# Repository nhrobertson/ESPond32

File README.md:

# ESPond32

A custom, self-hosted pond control system. An ESP32-S3 unit drives two pumps, a
water-fill valve, and a light, monitors pond water level with a float sensor, and is
controlled from a small web dashboard running on a Raspberry Pi over the local network.
It is the spiritual successor to the earlier, much simpler PondPi.

The device has no on-board web UI by design. All remote control happens over MQTT
between the firmware and the home server; the physical unit is fully functional on its
own (schedules, switches, leak lockout) even with the network down.

## System overview

```
  3-position switches          Raspberry Pi 3
  float sensor          WiFi   +-----------------------+
        |                LAN   | Mosquitto (MQTT broker)|
   +----v-----------+   <----> | espond-home-server     |  <-- browser
   | ESP32-S3 unit  |   MQTT   | (FastAPI dashboard)    |      (LAN / HTTPS)
   | (firmware)     |          +-----------------------+
   +----+-----------+
        | 3V3 GPIO
   +----v-----------+
   | SSR / relay    | ---> mains ---> pumps, valve, light
   +----------------+
```

- The firmware resolves output state from a strict precedence chain: leak lockout >
  physical switch > network override > schedule.
- The home server is the durable source of truth for configuration and schedules; the
  device only stores the last-applied config version.
- The MQTT wire contract between the two is documented in
  `software/espond-home-server/SPEC.md`.

## Repository layout

| Path | What it is |
|---|---|
| `software/espond32/` | Device firmware (ESP-IDF, C). See its README. |
| `software/espond-home-server/` | Raspberry Pi web dashboard + MQTT bridge (Python/FastAPI). See its README. |
| `hardware/` | KiCad projects (on-board and off-board SSR variants), BOMs, datasheets. See its README. |
| `ai_design_doc.pdf` | Original "Pond Control Unit — Design & Build Plan." Guidelines only; see disclosure below. |
| `LICENSE.md` | GNU GPL v3. |

## How this project was built (disclosure)

This repository mixes hand-written and AI-generated work, and it matters which is which:

- The **firmware** (`software/espond32/`) and the **hardware** (`hardware/`) were designed
  and written by hand by the project owner, with only minimal AI assistance.
- The **home server** (`software/espond-home-server/`) was generated almost entirely by an
  AI coding agent (Claude Code) working from a hand-authored spec. It has been deployed and
  works well, but should be reviewed like any AI-written code — particularly the auth and
  MQTT-handling paths — before being exposed beyond a trusted home LAN.
- `ai_design_doc.pdf` was an early planning document. It is **not** an accurate description
  of how the device actually works today; it is kept for historical context only. Where it
  conflicts with the firmware or `SPEC.md`, the firmware and `SPEC.md` win.

## Status

The off-board SSR hardware variant is finalized and in manufacturing. The firmware runs on
ESP32-S3 (developed/validated on a DevKitC). The home server is deployed on a Raspberry Pi 3.

## Safety

This system switches mains-voltage loads. Mains wiring, fusing, and enclosure work are the
integrator's responsibility. The float-fill and leak-lockout logic are failsafes, not
substitutes for correct plumbing, a hardware overflow path, and proper electrical practice.
Do not connect this to mains and water without understanding the whole chain.

## License

GNU General Public License v3. See `LICENSE.md`.

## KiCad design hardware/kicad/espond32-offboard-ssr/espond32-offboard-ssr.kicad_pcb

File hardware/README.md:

# ESPond32 Hardware

KiCad projects and supporting documents for the ESPond32 control board. The board carries
the ESP32-S3-WROOM-1 module, per-channel 3-position switches, the float-sensor input, a
WS2812 status LED chain, and the output-driver stage for four channels (pump1, pump2,
valve1, light1).

Designed by hand with only minimal AI assistance.

## Two board variants

There are two KiCad projects under `kicad/`, differing only in how the mains load is
switched:

| Project | Output stage | Mains on board? | Status |
|---|---|---|---|
| `kicad/espond32-offboard-ssr/` | 3.3V/5V logic-level control signal to an **external** SSR / relay module, driven through a MOSFET buffer | No - board is entirely SELV/low-voltage | **Finalized, in manufacturing** |
| `kicad/espond32-onboard-ssr/` | On-board optotriac + power triac SSR stage, mains terminals on the PCB | Yes | Design variant / reference |

The off-board variant is the primary build. It keeps all mains wiring off the PCB (each
channel just sinks an external module's control line to ground), which greatly simplifies
safety, layout, and enclosure work. The on-board variant is kept for anyone who wants a
single-board solution and is comfortable with mains-on-PCB design; it carries fuse, MOV,
isolated AC-DC, and per-channel triac + snubber parts.

Both variants match the firmware exactly: four output channels (not three), the WS2812 LED
chain on GPIO10, and the switch/float pin map from the firmware's `config.h`.

## Folder layout

```
hardware/
  kicad/
    espond32-offboard-ssr/   # primary board - schematic, PCB, exported BOM/CPL, JLCPCB output
    espond32-onboard-ssr/    # on-board-SSR variant
  bom/                       # STALE - see below
  datasheets/                # ESP32-S3-WROOM-1 datasheet
```

## Bill of materials

**The `bom/` folder at the top level is stale. Do not order from it.** The authoritative BOM
for each board is the one exported from its KiCad project (the `.csv` files inside each
`kicad/espond32-*/` directory, and the `jlcpcb/` outputs for the off-board variant). Treat
the KiCad project as the single source of truth for parts, footprints, and designators; the
top-level `bom/` CSVs predate the current schematics and are kept only for reference.

Key part choices worth knowing before a re-spin (from the current design):

- **Module:** ESP32-S3-WROOM-1-**N8** specifically (quad flash, no PSRAM). The N8R8/N16R8
  PSRAM variants use GPIO33-37, which collide with the firmware's debug test points.
- **Off-board output stage:** logic-level N-channel MOSFET (e.g. 2N7000) per channel buffers
  the GPIO up to a full logic swing before it reaches the external SSR/relay module, so the
  design works with the widest range of off-the-shelf 3-32 VDC modules. The external SSR
  modules themselves are not part of the board BOM.
- **Switches:** one 3-position center-off (ON/AUTO/OFF) toggle per channel; common to 3V3,
  the two throws to the SW-A/SW-B GPIOs. No external pulls (firmware configures pull-downs).
- **Float input:** TVS + series resistor + RC filter, sized for a long outdoor sensor run.
- **Indicators:** a single 6-pixel WS2812B chain (pump1, pump2, valve1, light1, float, sys),
  not discrete LEDs.

## KiCad libraries

The ESP32-S3-WROOM-1 symbol/footprint come from Espressif's official KiCad library
(install via KiCad's Plugin & Content Manager). Standard passives use the built-in KiCad
libraries. A few parts (3-position switch, some connectors) use custom footprints built from
their datasheets - see the project's footprint library.

## Manufacturing (off-board variant)

The `kicad/espond32-offboard-ssr/jlcpcb/` directory holds the Gerber/BOM/CPL output prepared
for JLCPCB assembly. Regenerate it from KiCad if you change the board; do not hand-edit the
exported files.

## Safety

The off-board board is low-voltage only and safe to handle and power from USB-C or a 5V
supply. Mains switching happens entirely in the external SSR modules and their wiring
harness - fusing, strain relief, and enclosure/creepage are the integrator's responsibility.

The on-board-SSR variant puts mains on the PCB and is only for people competent with
mains-voltage design: verify fuse rating, MOV placement, isolation/creepage clearances, and
snubber sizing against your actual loads before powering it.

## Provenance and disclosure

This hardware was designed by hand with minimal AI assistance. Note that `ai_design_doc.pdf`
(repo root) is an early planning document - it specifies three output channels and discrete
indicator LEDs, whereas the shipping design has four channels and a WS2812 chain to match the
firmware. Where the design doc and the KiCad projects disagree, the KiCad projects are
correct.

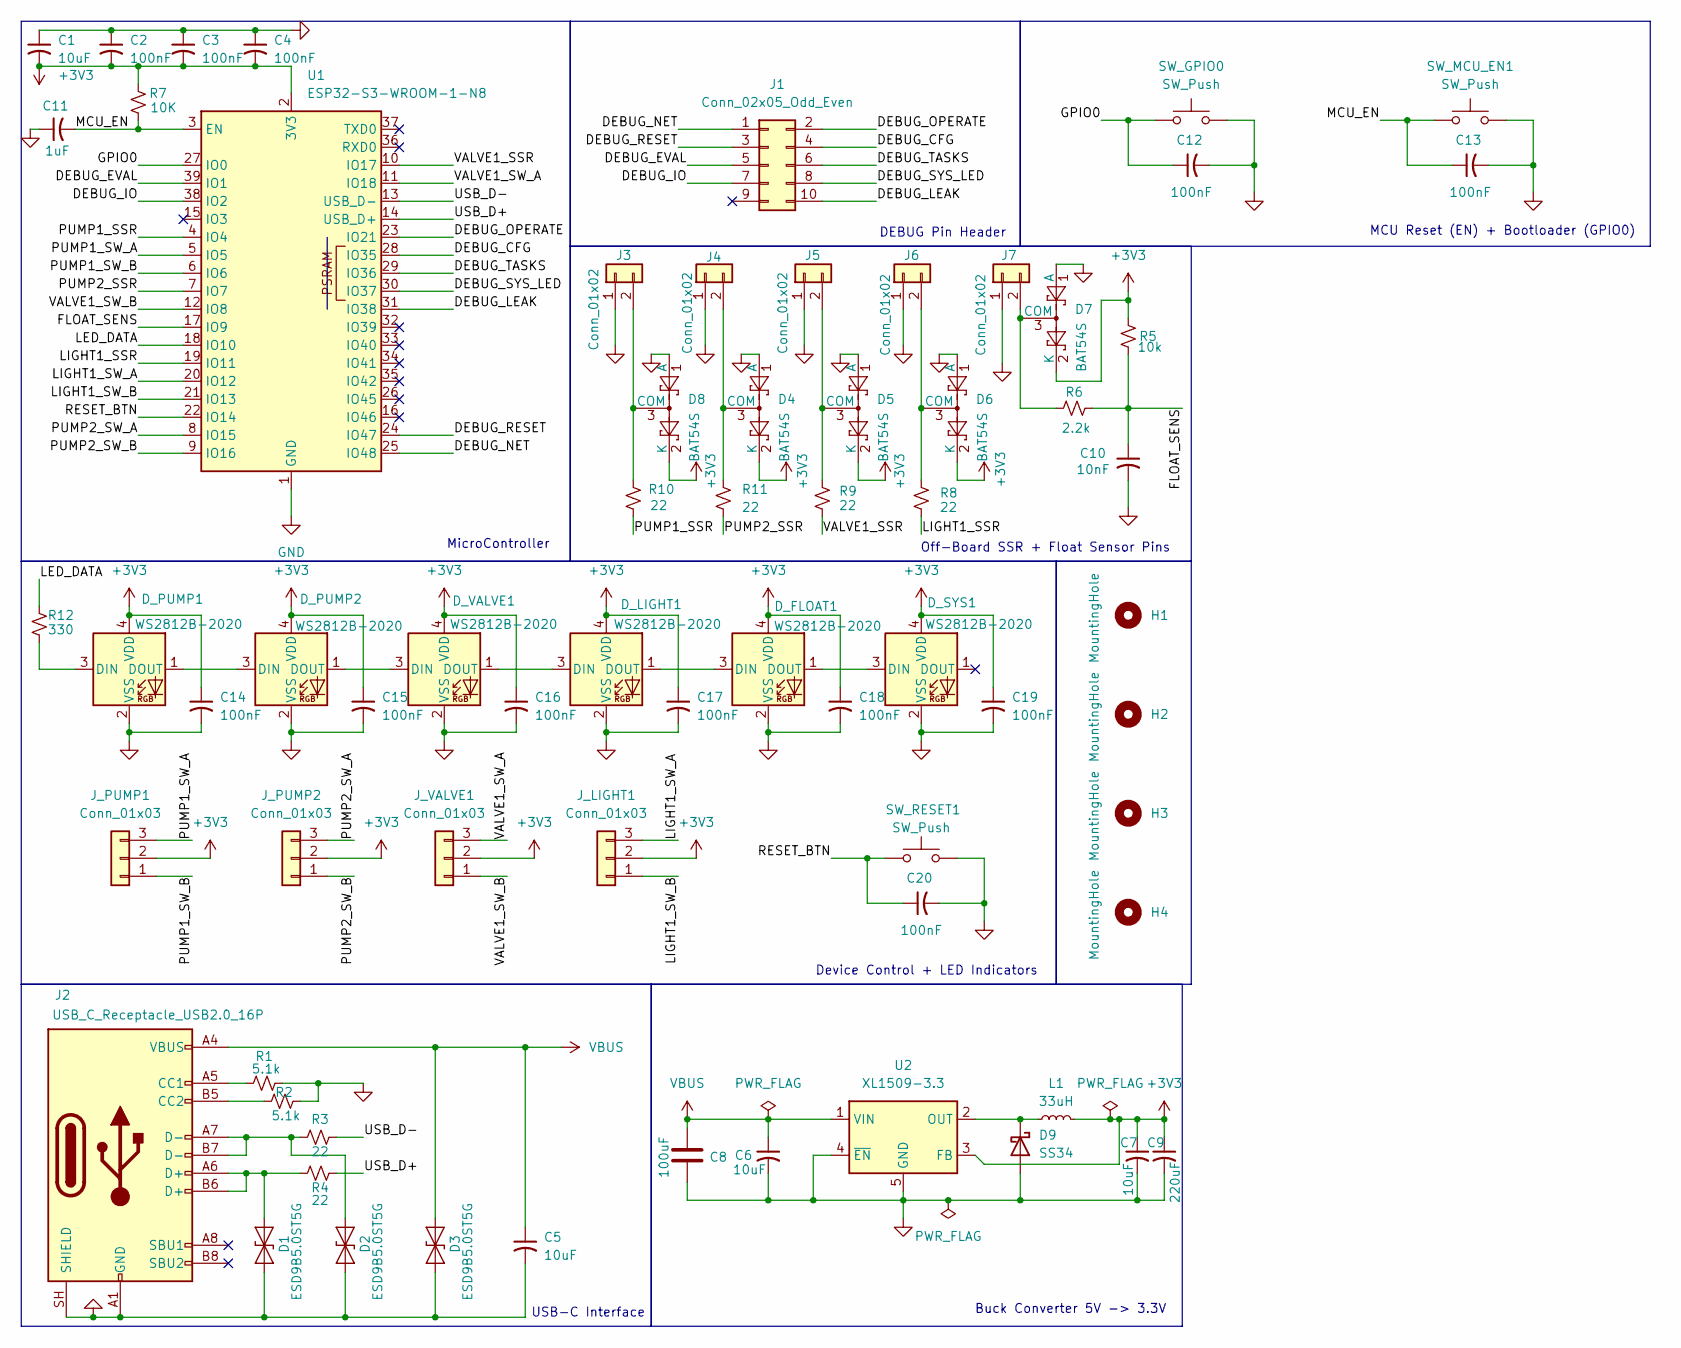
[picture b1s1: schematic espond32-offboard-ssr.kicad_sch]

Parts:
C1, C5, C6, C7: 10uF; C_0603_1608Metric
C2, C3, C4, C12, C13, C14, C15, C16, C17, C18, C19, C20: 100nF; C_0603_1608Metric
C8: 100uF; CP_Elec_6.3x7.7
C9: 220uF; CP_Elec_6.3x7.7
C10: 10nF; C_0603_1608Metric
C11: 1uF; C_0603_1608Metric
D1, D2, D3: ESD9B5.0ST5G; D_SOD-923
D4, D5, D6, D7, D8: BAT54S; SOT-23
D9: SS34; D_SMA
D_FLOAT1: WS2812B-2020; LED_WS2812B-2020_PLCC4_2.0x2.0mm
D_LIGHT1: WS2812B-2020; LED_WS2812B-2020_PLCC4_2.0x2.0mm
D_PUMP1, D_PUMP2: WS2812B-2020; LED_WS2812B-2020_PLCC4_2.0x2.0mm
D_SYS1: WS2812B-2020; LED_WS2812B-2020_PLCC4_2.0x2.0mm
D_VALVE1: WS2812B-2020; LED_WS2812B-2020_PLCC4_2.0x2.0mm
H1, H2, H3, H4: MountingHole; MountingHole_3.2mm_M3
J1: Conn_02x05_Odd_Even; PinHeader_2x05_P2.54mm_Vertical
J2: USB_C_Receptacle_USB2.0_16P; USB_C_Receptacle_HRO_TYPE-C-31-M-12
J3, J4, J5, J6, J7: Conn_01x02; TerminalBlock_Phoenix_MPT-0,5-2-2.54_1x02_P2.54mm_Horizontal
J_LIGHT1: Conn_01x03; JST_XH_B3B-XH-A_1x03_P2.50mm_Vertical
J_PUMP1, J_PUMP2: Conn_01x03; JST_XH_B3B-XH-A_1x03_P2.50mm_Vertical
J_VALVE1: Conn_01x03; JST_XH_B3B-XH-A_1x03_P2.50mm_Vertical
L1: 33uH; L_Sunlord_SWPA6045S
R1, R2: 5.1k; R_0603_1608Metric
R3, R4, R8, R9, R10, R11: 22; R_0603_1608Metric
R5: 10k; R_0603_1608Metric
R6: 2.2k; R_0603_1608Metric
R7: 10K; R_0603_1608Metric
R12: 330; R_0603_1608Metric
SW_GPIO0: SW_Push; SW_SPST_TL3342
SW_MCU_EN1: SW_Push; SW_SPST_TL3342
SW_RESET1: SW_Push; SW_SPST_TL3342
U1: ESP32-S3-WROOM-1-N8; ESP32-S3-WROOM-1
U2: XL1509-3.3; SOIC-8_3.9x4.9mm_P1.27mm

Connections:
+3V3: C1.2, C2.2, C3.2, C4.2, C7.1, C9.1, C14.1, C15.1, C16.1, C17.1, C18.1, C19.1, D4.2 (K), D5.2 (K), D6.2 (K), D7.2 (K), D8.2 (K), D_FLOAT1.4 (VDD), D_LIGHT1.4 (VDD), D_PUMP1.4 (VDD), D_PUMP2.4 (VDD), D_SYS1.4 (VDD), D_VALVE1.4 (VDD), J_LIGHT1.2, J_PUMP1.2, J_PUMP2.2, J_VALVE1.2, L1.2, R5.2, R7.2, U1.2 (3V3), U2.3 (FB)
/DEBUG_CFG: J1.4, U1.28 (IO35)
/DEBUG_EVAL: J1.5, U1.39 (IO1)
/DEBUG_IO: J1.7, U1.38 (IO2)
/DEBUG_LEAK: J1.10, U1.31 (IO38)
/DEBUG_NET: J1.1, U1.25 (IO48)
/DEBUG_OPERATE: J1.2, U1.23 (IO21)
/DEBUG_RESET: J1.3, U1.24 (IO47)
/DEBUG_SYS_LED: J1.8, U1.30 (IO37)
/DEBUG_TASKS: J1.6, U1.29 (IO36)
/FLOAT_SENS: C10.1, R5.1, R6.2, U1.17 (IO9)
/GPIO0: C12.1, SW_GPIO0.1, U1.27 (IO0)
/LED_DATA: R12.2, U1.18 (IO10)
/LIGHT1_SSR: R8.2, U1.19 (IO11)
/LIGHT1_SW_A: J_LIGHT1.3, U1.20 (IO12)
/LIGHT1_SW_B: J_LIGHT1.1, U1.21 (IO13)
/MCU_EN: C11.2, C13.1, R7.1, SW_MCU_EN1.1, U1.3 (EN)
/PUMP1_SSR: R10.2, U1.4 (IO4)
/PUMP1_SW_A: J_PUMP1.3, U1.5 (IO5)
/PUMP1_SW_B: J_PUMP1.1, U1.6 (IO6)
/PUMP2_SSR: R11.2, U1.7 (IO7)
/PUMP2_SW_A: J_PUMP2.3, U1.8 (IO15)
/PUMP2_SW_B: J_PUMP2.1, U1.9 (IO16)
/RESET_BTN: C20.1, SW_RESET1.1, U1.22 (IO14)
/USB_D+: R4.2, U1.14 (USB_D+)
/USB_D-: R3.2, U1.13 (USB_D-)
/VALVE1_SSR: R9.2, U1.10 (IO17)
/VALVE1_SW_A: J_VALVE1.3, U1.11 (IO18)
/VALVE1_SW_B: J_VALVE1.1, U1.12 (IO8)
GND: C1.1, C2.1, C3.1, C4.1, C5.2, C6.2, C7.2, C8.2, C9.2, C10.2, C11.1, C12.2, C13.2, C14.2, C15.2, C16.2, C17.2, C18.2, C19.2, C20.2, D1.2 (A2), D2.2 (A2), D3.2 (A2), D4.1 (A), D5.1 (A), D6.1 (A), D7.1 (A), D8.1 (A), D9.2 (A), D_FLOAT1.2 (VSS), D_LIGHT1.2 (VSS), D_PUMP1.2 (VSS), D_PUMP2.2 (VSS), D_SYS1.2 (VSS), D_VALVE1.2 (VSS), J2.A1 (GND), J2.A12 (GND), J2.B1 (GND), J2.B12 (GND), J2.SH (SHIELD), J3.1, J4.1, J5.1, J6.1, J7.1, R1.2, R2.2, SW_GPIO0.2, SW_MCU_EN1.2, SW_RESET1.2, U1.1 (GND), U1.40 (GND), U1.41 (GND), U2.4 (~EN), U2.5 (GND), U2.6 (GND), U2.7 (GND), U2.8 (GND)
unnamed: D1.1 (A1), J2.A6 (D+), J2.B6 (D+), R4.1
unnamed: D2.1 (A1), J2.A7 (D-), J2.B7 (D-), R3.1
unnamed: D4.3 (COM), J4.2, R11.1
unnamed: D5.3 (COM), J5.2, R9.1
unnamed: D6.3 (COM), J6.2, R8.1
unnamed: D7.3 (COM), J7.2, R6.1
unnamed: D8.3 (COM), J3.2, R10.1
unnamed: D9.1 (K), L1.1, U2.2 (OUT)
unnamed: D_FLOAT1.3 (DIN), D_LIGHT1.1 (DOUT)
unnamed: D_FLOAT1.1 (DOUT), D_SYS1.3 (DIN)
unnamed: D_LIGHT1.3 (DIN), D_VALVE1.1 (DOUT)
unnamed: D_PUMP1.3 (DIN), R12.1
unnamed: D_PUMP1.1 (DOUT), D_PUMP2.3 (DIN)
unnamed: D_PUMP2.1 (DOUT), D_VALVE1.3 (DIN)
unnamed: J2.A5 (CC1), R1.1
unnamed: J2.B5 (CC2), R2.1
VBUS: C5.1, C6.1, C8.1, D3.1 (A1), J2.A4 (VBUS), J2.A9 (VBUS), J2.B4 (VBUS), J2.B9 (VBUS), U2.1 (VIN)

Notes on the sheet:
USB-C Interface
MCU Reset (EN) + Bootloader (GPIO0)
Device Control + LED Indicators
Buck Converter 5V -> 3.3V
Off-Board SSR + Float Sensor Pins
DEBUG Pin Header
MicroController

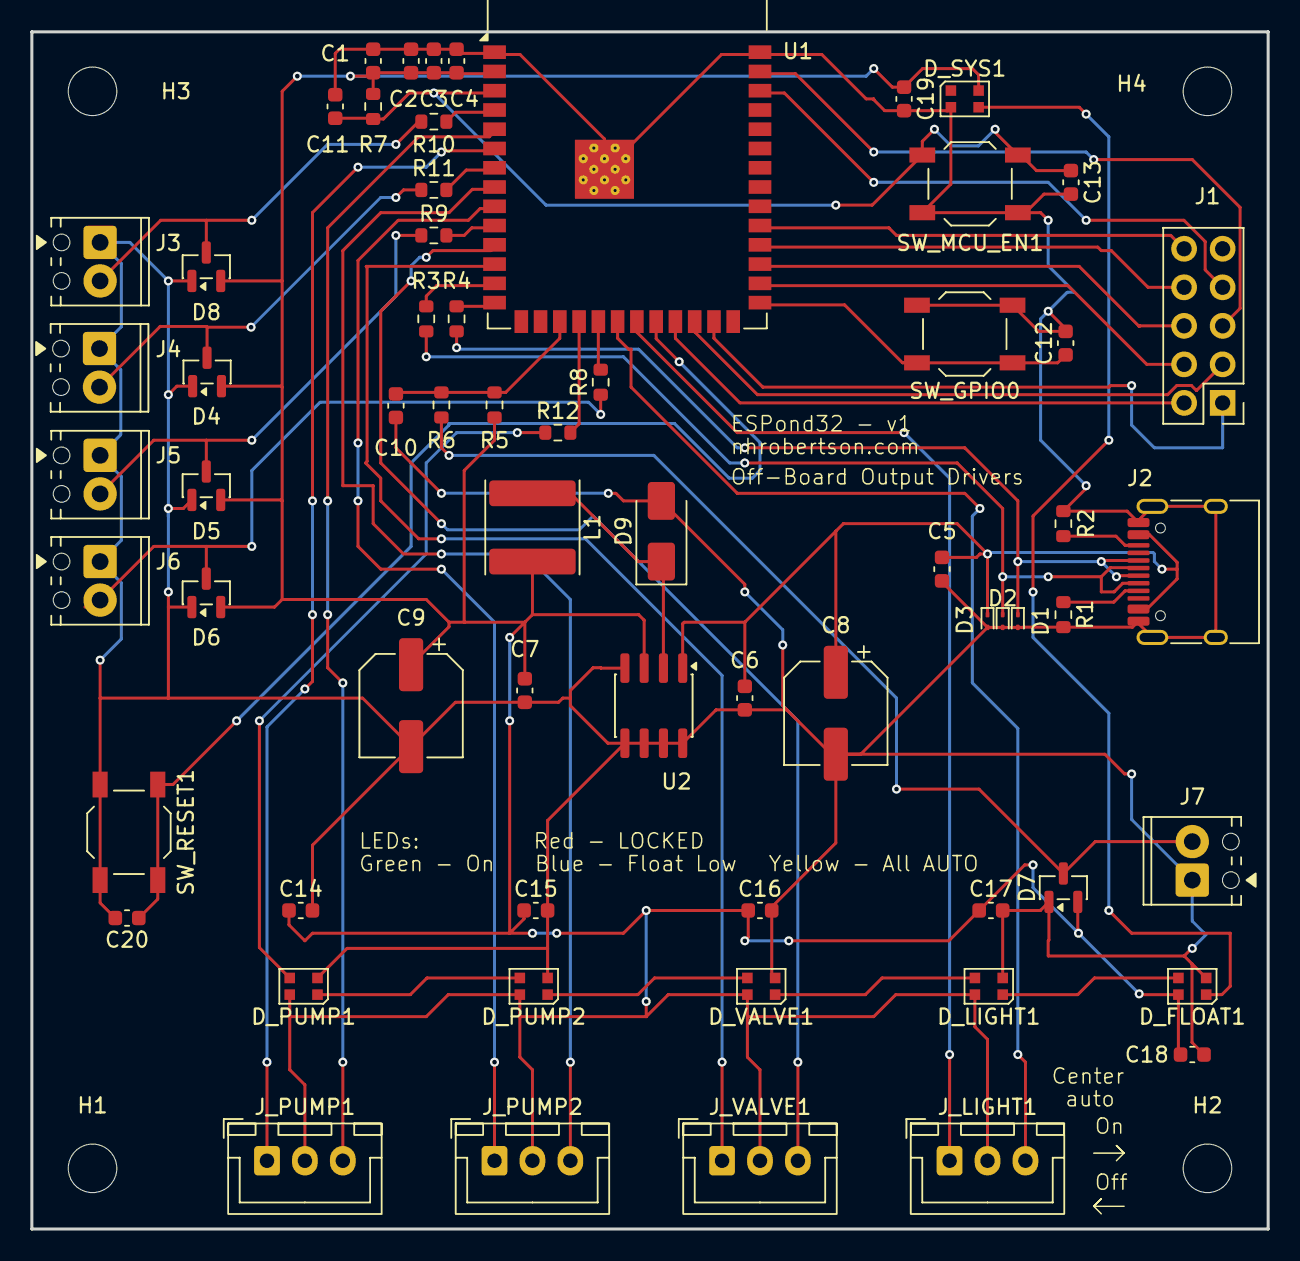
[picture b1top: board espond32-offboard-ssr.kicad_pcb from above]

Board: 2 copper layers, 81.5 x 78.9 mm, 68 parts (0 on the bottom side), 47 nets.

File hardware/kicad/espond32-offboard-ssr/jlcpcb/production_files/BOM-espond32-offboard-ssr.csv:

Comment,Designator,Footprint,LCSC,Quantity
100nF,"C12,C13,C14,C15,C16,C17,C18,C19,C2,C20,C3,C4",C_0603_1608Metric,C14663,12
100uF,C8,CP_Elec_6.3x7.7,C15008,1
10K,R7,R_0603_1608Metric,C25804,1
10k,R5,R_0603_1608Metric,C25804,1
10nF,C10,C_0603_1608Metric,C57112,1
10uF,"C1,C5,C6,C7",C_0603_1608Metric,C96446,4
1uF,C11,C_0603_1608Metric,C15849,1
2.2k,R6,R_0603_1608Metric,C4190,1
22,"R10,R11,R3,R4,R8,R9",R_0603_1608Metric,C23345,6
220uF,C9,CP_Elec_6.3x7.7,C2036,1
330,R12,R_0603_1608Metric,C23138,1
33uH,L1,L_Sunlord_SWPA6045S,C83451,1
5.1k,"R1,R2",R_0603_1608Metric,C23186,2
BAT54S,"D4,D5,D6,D7,D8",SOT-23,C7420333,5
ESD9B5.0ST5G,"D1,D2,D3",D_SOD-923,C111566,3
ESP32-S3-WROOM-1-N8,U1,ESP32-S3-WROOM-1,C2913198,1
SS34,D9,D_SMA,C7420365,1
SW_Push,"SW_GPIO0,SW_MCU_EN1,SW_RESET1",SW_SPST_TL3342,C2886894,3
USB_C_Receptacle_USB2.0_16P,J2,USB_C_Receptacle_HRO_TYPE-C-31-M-12,C165948,1
WS2812B-2020,"D_FLOAT1,D_LIGHT1,D_PUMP1,D_PUMP2,D_SYS1,D_VALVE1",LED_WS2812B-2020_PLCC4_2.0x2.0mm,C965555,6
XL1509-3.3,U2,SOIC-8_3.9x4.9mm_P1.27mm,C2681226,1
Conn_01x02,J3,"TerminalBlock_Phoenix_MPT-0,5-2-2.54_1x02_P2.54mm_Horizontal",,1
Conn_01x03,J_VALVE1,JST_XH_B3B-XH-A_1x03_P2.50mm_Vertical,,1
Conn_01x03,J_PUMP1,JST_XH_B3B-XH-A_1x03_P2.50mm_Vertical,,1
Conn_01x02,J4,"TerminalBlock_Phoenix_MPT-0,5-2-2.54_1x02_P2.54mm_Horizontal",,1
Conn_01x02,J7,"TerminalBlock_Phoenix_MPT-0,5-2-2.54_1x02_P2.54mm_Horizontal",,1
Conn_02x05_Odd_Even,J1,PinHeader_2x05_P2.54mm_Vertical,,1
Conn_01x02,J6,"TerminalBlock_Phoenix_MPT-0,5-2-2.54_1x02_P2.54mm_Horizontal",,1
Conn_01x03,J_PUMP2,JST_XH_B3B-XH-A_1x03_P2.50mm_Vertical,,1
Conn_01x02,J5,"TerminalBlock_Phoenix_MPT-0,5-2-2.54_1x02_P2.54mm_Horizontal",,1
Conn_01x03,J_LIGHT1,JST_XH_B3B-XH-A_1x03_P2.50mm_Vertical,,1

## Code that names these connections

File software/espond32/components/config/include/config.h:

#ifndef CONFIG_H
#define CONFIG_H

#define NUM_OUTPUTS       4
#define NUM_INPUTS        1
#define NUM_DEVICES       (NUM_OUTPUTS + NUM_INPUTS)


#define NUM_PUMPS         2
#define NUM_VALVES        1
#define NUM_LIGHT         1
#define NUM_FLOAT         1

#define NUM_LEDS          (NUM_DEVICES + 1) //1 - Pump 1, 2 - Pump 2, 3 - Valve 1, 4 - Light 1, 5 - Float Sensor

#define DEBOUNCE_SAMPLES      5
#define MAX_FILL_MIN          25  //Max continuous fill duration before lockout (stuck float failsafe)
//GPIO Definitions
#define PUMP1_SSR_GPIO        GPIO_NUM_4
#define PUMP1_SW_A_GPIO       GPIO_NUM_5
#define PUMP1_SW_B_GPIO       GPIO_NUM_6
#define PUMP1_LED_PIX         0

#define PUMP2_SSR_GPIO        GPIO_NUM_7
#define PUMP2_SW_A_GPIO       GPIO_NUM_15
#define PUMP2_SW_B_GPIO       GPIO_NUM_16
#define PUMP2_LED_PIX         1

#define VALVE1_SSR_GPIO       GPIO_NUM_17
#define VALVE1_SW_A_GPIO      GPIO_NUM_18
#define VALVE1_SW_B_GPIO      GPIO_NUM_8
#define VALVE1_LED_PIX        2

#define LIGHT1_SSR_GPIO       GPIO_NUM_11
#define LIGHT1_SW_A_GPIO      GPIO_NUM_12
#define LIGHT1_SW_B_GPIO      GPIO_NUM_13
#define LIGHT1_LED_PIX        3

#define FLOAT1_SENS_GPIO      GPIO_NUM_9
#define FLOAT1_LED_PIX        4


#define LED_DATA_GPIO         GPIO_NUM_10

#define RESET_BTN_GPIO        GPIO_NUM_14

#define SYS_LED_PIX           5


#define DEBUG_INDEPTH_LOG     1
#define DEBUG_GPIO_ENABLE     1

#define DEBUG_GPIO_OPERATE    GPIO_NUM_21   //task_operate      (Core 1, 50ms)
#define DEBUG_GPIO_EVAL       GPIO_NUM_1    //task_evaluate_cfg (Core 1, 250ms)
#define DEBUG_GPIO_IO         GPIO_NUM_2    //task_check_io     (Core 1, 10ms)
#define DEBUG_GPIO_LEAK       GPIO_NUM_38   //task_check_leak   (Core 1, 10ms)
#define DEBUG_GPIO_RESET      GPIO_NUM_47   //task_check_for_reset (Core 1, 50ms)
#define DEBUG_GPIO_NET        GPIO_NUM_48   //task_net_manager  (Core 0, event-driven)
#define DEBUG_GPIO_CFG        GPIO_NUM_35   //task_check_cfg    (Core 0, event-driven)
#define DEBUG_GPIO_TASKS      GPIO_NUM_36   //task_listen_for_task_event (Core 1, event-driven)
#define DEBUG_GPIO_SYS_LED    GPIO_NUM_37   //task_set_sys_light (Core 1, 1000ms)


#endif //CONFIG_H

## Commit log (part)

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2026-06-17 First commitment
2026-06-17 Added nvim configs for clangd lsp and blink example project as base for purposes of ensuring building
2026-06-18 Added configuation file and began working on the models
2026-06-24 Added components, basic I/O
2026-06-25 Worked a lot on starting on lower level peripherals and abstracting to help simiplify development later
2026-06-25 more work on io
2026-06-26 Lots of work on I/O and LED - device initalization base almost done
2026-06-26 Code is building
2026-06-27 setup tasks component
2026-06-30 More stuff added
2026-06-30 added cJSON dependency
